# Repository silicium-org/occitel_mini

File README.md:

# [Occitel Mini](https://silicium.org/index.php/edition/occitel-mini-2), production (c)2020..2025 by [Silicium](http://silicium.org)

## TL;DR

[Occitel Mini](https://silicium.org/index.php/edition/occitel-mini-2) is a 1:2 scale reproduction of the original [Occitel](https://silicium.org/index.php/blog-catalogue/pongs/societe-occitane-d-electronique-occitel) game console released in 1976 by the [Société occitane d'électronique](https://fr.wikipedia.org/wiki/Société_occitane_d%27électronique), powered by the then brand-new [General Instruments](https://fr.wikipedia.org/wiki/General_Instrument) [AY-3-8500](https://fr.wikipedia.org/wiki/AY-3-8500) like every Pong-on-a-chip of the same era.

We manufactured a small batch #1, and who knows if there will ever be a batch #2…
Get one from us by [contacting Silicium](https://silicium.org/index.php/contactez-nous) or visit us [IRL at events](https://www.facebook.com/siliciumasso/photos/le-tgs-au-meett-de-toulouse-cétait-du-30-novembre-au-1er-décembre-si-vous-lavez-/1154207946707585/) such as the [Toulouse Game Show](https://tgs-toulouse.fr). \
It comes with a 70-page full color booklet filled with historical data, interviews, new and old photos, in a cardboard package that also is a 1:2 scale reproduction of the original, including cover art that only the connoisseur will know to appreciate…

### QuickStart
- plug into your TV A/V-in with a 75Ω composite lead
- plug in the supplied paddles
- connect a USB Micro-B cable to any power supply
  - caution: Occitel Mini draws _so little_ that a USB power bank may go to sleep
  - you can power and reprogram from any computer running the [Arduino IDE](https://www.arduino.cc/en/software)
- switch on the `game mode` selector
  - you will see 2 LEDs glowing through the case, blinking as the ball hits rackets—if they stop blinking, the software froze ⇒ please file a bug report
  - consult your 1976 Occitel manual regarding other controls
- by default, Occitel Mini emulates the 1976 revision of the AY-3-8500 chip—long-pressing `RàZ` alternates with the 1977 version
- the motherboard has a jumper for NTSC rather than PAL composite video: you may bridge the pads, or solder in a jumper or switch

### Legal
The family of the founder of Société Occitane d'Electronique gave association Silicium permission to reproduce and adapt their designs.

The Occitel book is copyrighted association Silicium in Toulouse, France, licensed under Creative Commons CC-BY-NC-SA.

Grant Searle did not explicit under what license he published his AVRPong a.k.a TVGame 1.5. He wrote "I hope this page has been useful" suggesting it is there for others to use (in other words, he must have meant the opposite of "all rights reserved"), "All information shown here is supplied "as is" with no warranty whatsoever" which is an element of typical licenses but does not grant any rights, "All copyrights recognised" which suggests he recognizes others copyright in prior works he derived his from.

However his Arduino source code is a single file that includes a copy of the Arduino TVout library and its license text, that happens to be the MIT license, therefore we interpret that the whole source code and by extension, the hardware schematics, are released under the MIT license.

The Occitel Mini schematics are a derivative work of Grant Searle's original work, with changes (c)Silicium, combination licensed under the MIT license.

The Occitel source code is a derivative work of TVout by Myles Metzer, with changes (c)Avamander, (c)Grant Searle, (c)members of Silicium (see list in [TL;DR](#tldr)), combination licensed under the MIT license.

The PCB and 3d-printed design are (c)members of Silicium, licensed under CC-BY-NC-SA.

## Changelog
Known bugs: none, unless there is still something wrong with the score in squash (single-player) game ??

Batch #1:
- PCB **1.5.0** (KiCAD 8.0)
- 3d-printed case **2024-11-19** (Fusion 360 -> STEP, STL)
- software **2025-01-11** for SparkFun Pro Micro ATmega32U4 (Arduino IDE 2.3)
- Git tag **1.0** public release and production batch #1

_Authors: Alain Trentin, ben*.* "foobarbaz", François "admin" Pussault, René "El Presidente" Speranza, Sébastien "Sebcbien" Périn, Simon "Nakwada" \
Supermodels: Jeff "Pocket" L., PStriolo_

Initial prototype on [Arduino Leonardo](https://store.arduino.cc/collections/boards-modules/products/arduino-leonardo-with-headers), then [SparkFun Pro Micro](https://www.SparkFun.com/pro-micro-5v-16mhz.html) on breadbord.
Initial schematics on [EasyEDA](https://easyeda.com/).

TODO: easter egg in sleep mode. OC6000 mini with AY-3-8610 emulation using X/Y joysticks on TRRS jacks.

## Design
### Principles of operation
#### The original

The 1976 Occitel is a standard application of the General Instrument AY-3-8500, outputting to a UHF modulator for French TV sets (SECAM 50Hz - there is not much difference with PAL as the Occitel is black&white).
It has an internal speaker and runs off 2 4.5V internal batteries or an external 9V transformer.

 \

Initially it had linear potentiometers in the main case, like the Téléscore 750 from SEB, but apparently it was decided to switch to external paddles, by bolding 3.5mm jack receptacles on the sides, wired in lieu of the integrated linear potentiometers, that were still installed but non-functional - it must have been quicker and less expensive to leave the linear potentiometer in place rather than making new injection molds.

#### The Mini
 \

Grant Searle having reverse-engineered the AY-3-8500 and implemented an emulator for ATmega328, all that was left to do was:
- convert to ATmega32U4 (there are differences in the hardware timers)
- set ball speed and paddle size according to the 3 difficulty settings of the Occitel
- fix a few bugs (the software runs for days, whereas the original crashed after an hour or so - we believe this was due to non-atomic variables shared between background and interrupt contexts).

There is no speaker in the Occitel Mini, instead you get an line-level mono audio output, compatible with any TV set A/V-in.

#### Paddles
 \

Occitel Mini has detachable paddles like the original.
Audio jacks as in the original Occitel are fine for 2-wire RC timing measurement as done by AY-3-8500, but are less than ideal for 3-wire potentiometric measurement as they are prone to shorting the contacts on insertion, which causes arcing between the ground and +5V rails and depending on your USB power supply, may brown out the CPU, causing the video to go out.

That problem is fixed by adding a current-limiting series resistor on the high side of the paddles' potentiometer.

#### Bit-banged composite video
Bit-banged composite video for Arduino was created by Avamander.
ATmega microcontrollers have no DMA and their SPI does not seem to be adequate as a shift register for gap-less pixel rendering, so assembly code toggles a GPIO one pixel at a time, using NOPs for horizontal timing.
Hardware timers are used for vertical timing, so there can be code in the background, and this is where the game logic runs, thus its timing is not critical.
Nonetheless, Pong is simple enough that Grant's code runs at full FPS.

Hardware-wise, we preferred to mix the luminance and sync GPIO outs with diodes (wired-or by diode-resistor logic) rather than pure resistors. This is a change made by JasonKits.

The mixing is passive, relying on the 75Ω termination in the composite video input of the TV set.

If you leave the video output unconnected, voltages will be wrong and an oscilloscope configured for video trigger may fail to recognize the composite sync. Just plug in a screen, or an external termination resistor.

#### ATmega328P vs. ATmega32U4
 \

On ATmega328P, Grant Searle used PB1(OC1A) for SYNC, PB2(OC1B) for VID and PB3(OC2A) for AUD.
Grant's original source code would run on an Arduino Uno wired as SYNC on pin D9, VID on pin D10, AUD on pin D11.

In fact VID and SYNC can be any pins as they are actually not used as OC1x. Also they do not have to be the MSB of a port data register, as imposed by recent versions of the TVout library.

ATmega32U4 does not have 8-bit timer 2 but has timer 0, so we reassigned AUD to timer 0.

Leonardo has a pin for OC0A (PB7 on pin D11) that can serve as AUD, but SparkFun Pro Micro does not.

OC0A is not available on SparkFun Pro Micro, but OC0B is on pin 0. So if OC0A and OC0B are loaded with the same value, timer 0 in CTC mode will do PWM based on OC0A and OC0B will output the toggled waveform same as OC0A (at worst, off by 1 timer increment).

So that is why AUD must be on SparkFun Pro Micro pin 3 (PD0 as OC0B).
VID is PB4 on pin 8 and SYNC is PB5 on pin 9.

On Leonardo, that would be VID on pin D8, SYNC on pin D9. And yes, the SparkFun Pro Micro numbering matches the Leonardo whenever possible.

While not necessary, the Pro Micro technique is compatible with Leonardo, if AUD is on pin D3 (that also is PD0).

### Making your own
- Send the [Gerber](./production_batch_1/occitel_mini-gerber+drill.zip) to JLCPCB or PCBWay etc.
- Solder in the [BoM](./production_batch_1/doc/occitel%20mini%20bom.csv) according to the [schematics](./production_batch_1/doc/occitel%20mini%20sch.pdf) and [layout](./production_batch_1/doc/occitel%20mini%20pcb.pdf)
  - Resistors are 1/8W through-hole or SMD (twin footprints).
  - Diodes are any fast small-signals Si diodes, 1N4007, 1N4148…
  - The audio DC-blocking capacitor can be any value in the μF range.
  - All 3 slide switches are the same SP5T, range-limited by the openings in the case. We found it on AliExpress, see the ["datasheet"](./kicad/1p5t_vertical.jpg). They have to be soldered such that the pins do not protrude from the bottom of the PCB, and the slider caps will be at just the right height. We 3d-printed a jig for holding the SP5T in place while soldering. YMMV…
  - the long-stem (13mm) and right-angle microswitches are common enough. You can use a different length and compensate for the length with the depth of the 3d-printed pushbutton caps.
- Obtain a SparkFun Pro Micro 5V/16MHz or clone and flash the [sketch](./Arduino/occitel_mini/occitel_mini.ino) (see [Contribute](#contribute) if you do not see SparkFun board options in the Arduino IDE).
> [!WARNING]
> The Arduino IDE has no way to know if you have a 8 or 16MHz Pro Micro, which this is critical to USB operation. Unfortunately 8MHz is the 1st menu entry.
> **Be sure to manually set cpu="ATmega32U4 (5V, 16 MHz)"**. Double-check board=="SparkFun Pro Micro" in case the IDE did not detect the USB PID/VID. See below for unbricking.
- Print the [enclosure](./production_batch_1/3d_print/) (the case is a 2-color print, [orange](./production_batch_1/3d_print/boitier.stl) and [white](./production_batch_1/3d_print/serigraphie.stl))
- Solder wires between the female 3.5mm jacks and motherboard (directly or using any connector with 0.1" spacing).
- Slice a 3.5mm audio jack patch cord (male-male) in half and solder each half to a 10kΩ potentiometer, to be installed in each paddle. For easy soldering, use stereo audio cable with individually jacketed left and right wires, not enamel-insulated bare copper strands.
- Assemble with M3x8 self-tapping screws.

### Modifying
- Circuit board: open [`kicad/occitel_mini`](./kicad/occitel_mini/) in [KiCAD](https://www.kicad.org) 8.x
  - beginners may prefer the [EasyEDA](https://easyeda.com/) [standard](https://easyeda.com/editor) or [pro](https://pro.easyeda.com/editor) online editors: import `historical/EasyEDA/SCH_occitel_mini.json` but be warned that the schematics is slightly outdated (no short-circuit protection at the paddle jacks) and was never routed in EasyEDA (routing done only in KiCAD)
  - alternatively, the circuit is easily constructed on a breadbord or perfboard
- Software: copy [`Arduino/occitel_mini/`](./Arduino/occitel_mini/) to your `Arduino/` folder
  - MacOS: `/Users/$USER/Documents/Arduino/`
  - Linux: `/home/$USER/Documents/Arduino/`
  - Windows: `C:\Users\%USERNAME%\Documents\Arduino\`
  - In order to see SparkFun options in the Arduino IDE board manager, you will need to add `https://raw.githubusercontent.com/sparkfun/Arduino_Boards/master/IDE_Board_Manager/package_sparkfun_index.json` to Settings. Or just use `Arduino Leonardo`.

#### Unbricking
If you brick your Pro Micro, [press the reset microswitch twice](https://cdn.SparkFun.com/datasheets/Dev/Arduino/Boards/32U4Note.pdf) within about 0.5s and you will have 8 seconds to press the `Download` button.

If all else fail, the motherboard has the standard Arduino ICSP header (unpopulated—solder a 3x2 HE10 header, or just unplug the Pro Micro module and use DuPont flying leads) that you can use to reflash the bootloader with an [STK500](https://www.microchip.com/en-us/development-tool/atstk500) (just kidding! get an AVR Dragon or the [Olimex AVR-ISP500-TINY](https://www.olimex.com/Products/AVR/Programmers/AVR-ISP500-TINY/)) programmer or the Arduino IDE menu [`Tools > Programmer > Arduino as ISP`](https://docs.arduino.cc/built-in-examples/arduino-isp/ArduinoISP/).

#### Source code
There are 2 compile-time settings:
- `DEBUG_CONSOLE` enables a rudimentary debugger on the serial console, that takes single-character commands `h`, `v`, `o`, `s`, `d`, `r`.
  - while useful if you do no have a DebugWire probe, the Arduino standard library for serial-over-USB appears unreliable in the presence of our direct timer programming, which is non-negociable for bit-banged video generation, so it is what it is.
- `SERIAL_USB_WAIT_DELAY_MS` is 1ms for fastest boot in the production build, but can be set e.g. to 1500ms so that the Arduino IDE serial monitor will have time to capture the early logs.

There are no other compile-time user settings, but you can change many things if you want to add games and depart from strict AY-3-8500 emulation.

You can also run `occitel_mini.ino` on other Arduino boards by selecting adequate assignments of timers and ATmega pins wired to your board's connectors.
See analysis in [ATmega328P vs. ATmega32U4](#atmega328p-vs-atmega32u4) and comments in the source code.

#### Extensibility
ADC pins A2 and A3 are unused (hence why we ran out of inputs for 1976/1977 AY-3-8500 selection) and could be used for 2 more potentiometer, for 4-player Pong, or Occitel OC6000 emulation and its mesmerizing AY-3-8610 soccer game where you can go not just up and down but also left and right… Revolutionary!

Democoders have output color video on ATmega, even on ATtiny.
There are 2 schools, RGB with resistor ladders as a crude DAC, and composite video.
Black&white composite video needs a single GPIO for luminance, and the color RGB resistor ladder technique can be used for greyscale.

PAL/NTSC Color composite is harder because a 4.43MHz color burst is needed for PAL (3.58MHz for NTSC), and then phase lock must be maintained.
This is not realistic on ATmega32U4 that is not fast enough to oversample the color burst by an integer ratio, and whose clock cannot be changed or else USB won't work.

But NTSC has been pulled off by democoders on ATmega328P overclocked to 28MHz by swapping the crystal, yielding a 8x oversampling of the colorburst, enough to obtain a few discrete digital phase shifts, exactly how Woz did it on the Apple II…

At that point, one might as well switch to an ESP32 or STM32 with DMA bit-banged video, or better, a Parallax Propeller or Raspberry Pi Pico (and its XMOS-inspired software-defined signal-shaping coprocessors), or a Raspberry Pi Zero as in the RGB2HDMI…

## Bibliography
### General Instruments AY-3-8500
- [www.pong-story.com](https://www.pong-story.com/gi.htm)
  _trad [fr](https://www-pong--story-com.translate.goog/gi.htm?_x_tr_sl=auto&_x_tr_tl=en&_x_tr_hl=fr&_x_tr_pto=wapp)_
- Occitel Mini would not exist without the amazing [work of Grant Searle](http://searle.x10host.com/AVRPong/index.html)
  _trad [fr](https://searle-x10host-com.translate.goog/AVRPong/index.html?_x_tr_sch=http&_x_tr_sl=auto&_x_tr_tl=en&_x_tr_hl=fr&_x_tr_pto=wapp)_
- Giancarlo Zuliani also did some reverse-engineering: [Analisi del gioco Pong](https://gzuliani.github.io/games/pong-emulator.html)
  _trad [fr](https://gzuliani-github-io.translate.goog/games/pong-emulator.html?_x_tr_sl=auto&_x_tr_tl=fr&_x_tr_hl=fr&_x_tr_pto=wapp)
       [en](https://gzuliani-github-io.translate.goog/games/pong-emulator.html?_x_tr_sl=auto&_x_tr_tl=en&_x_tr_hl=fr&_x_tr_pto=wapp)_
- Joris van Looveren implemented Grant Searle's design on a [custom PCB](http://joris.van-looveren.net/projects/avrpong/)
- JasonKits sells an [assembled board](https://www.tindie.com/products/jasonkits/classic-70s-pong-game/#product-description)
- Reverse engineering by [Cole Johnson](https://nerdstuffbycole.blogspot.com)
  - [Reverse Engineering the AY-3-8500, part 1: Demystifying the Pins](https://nerdstuffbycole.blogspot.com/2018/01/reverse-engineering-ay-3-8500-part-1.html)
  _trad [fr](https://nerdstuffbycole-blogspot-com.translate.goog/2018/01/reverse-engineering-ay-3-8500-part-1.html?_x_tr_sl=auto&_x_tr_tl=en&_x_tr_hl=fr&_x_tr_pto=wapp)_
  - [Building a Simulation of the AY-3-8500](https://nerdstuffbycole.blogspot.com/2018/04/building-simulation-of-ay-3-8500.html)
  _trad [fr](https://nerdstuffbycole-blogspot-com.translate.goog/2018/04/building-simulation-of-ay-3-8500.html?_x_tr_sl=auto&_x_tr_tl=fr&_x_tr_hl=fr&_x_tr_pto=wapp)_
  - [The Simulation is Finally Complete!*](https://nerdstuffbycole.blogspot.com/2018/08/the-simulation-is-finally-complete.html)
  _trad [fr](https://nerdstuffbycole-blogspot-com.translate.goog/2018/08/the-simulation-is-finally-complete.html?_x_tr_sl=auto&_x_tr_tl=fr&_x_tr_hl=fr&_x_tr_pto=wapp)_
  - [Control and Sync Generation in the AY-3-8500](https://nerdstuffbycole.blogspot.com/2018/08/control-and-sync-generation-in-ay-3-8500.html)
  _trad [fr](https://nerdstuffbycole-blogspot-com.translate.goog/2018/08/control-and-sync-generation-in-ay-3-8500.html?_x_tr_sl=auto&_x_tr_tl=fr&_x_tr_hl=fr&_x_tr_pto=wapp)_
  - [Entering the Retrochallenge! (09/2018)](https://nerdstuffbycole.blogspot.com/2018/09/entering-retrochallenge-092018.html)
  _trad [fr](https://nerdstuffbycole-blogspot-com.translate.goog/2018/09/entering-retrochallenge-092018.html?_x_tr_sl=auto&_x_tr_tl=fr&_x_tr_hl=fr&_x_tr_pto=wapp)_
  - [Games and Field Generation in the AY-3-8500](https://nerdstuffbycole.blogspot.com/2018/09/games-and-field-generation-in-ay-3-8500.html)
  _trad [fr](https://nerdstuffbycole-blogspot-com.translate.goog/2018/08/control-and-sync-generation-in-ay-3-8500.html?_x_tr_sl=auto&_x_tr_tl=fr&_x_tr_hl=fr&_x_tr_pto=wapp)_
  - [A visual simulation of the SP0256 (beta)](https://nerdstuffbycole.blogspot.com/2018/09/a-visual-simulation-of-sp0256-beta.html)
  _trad [fr](https://nerdstuffbycole-blogspot-com.translate.goog/2018/09/a-visual-simulation-of-sp0256-beta.html?_x_tr_sl=auto&_x_tr_tl=fr&_x_tr_hl=fr&_x_tr_pto=wapp)_
  - [Shifting bits: How a PONG chip generates on-screen scores](https://nerdstuffbycole.blogspot.com/2018/09/shifting-bits-how-pong-chip-generates.html)
  _trad [fr](https://nerdstuffbycole-blogspot-com.translate.goog/2018/09/shifting-bits-how-pong-chip-generates.html?_x_tr_sl=auto&_x_tr_tl=fr&_x_tr_hl=fr&_x_tr_pto=wapp)_
  - [RetroChallenge 2018 wrap up... and whats next](https://nerdstuffbycole.blogspot.com/2018/10/retrochallenge-2018-wrap-up-and-whats.html)
  _trad [fr](https://nerdstuffbycole-blogspot-com.translate.goog/2018/10/retrochallenge-2018-wrap-up-and-whats.html?_x_tr_sl=auto&_x_tr_tl=fr&_x_tr_hl=fr&_x_tr_pto=wapp)_
  - [Progress update on AY-3-8500 emulation](https://nerdstuffbycole.blogspot.com/2019/01/progress-update-on-ay-3-8500-emulation.html)
  _trad [fr](https://nerdstuffbycole-blogspot-com.translate.goog/2019/01/progress-update-on-ay-3-8500-emulation.html?_x_tr_sl=auto&_x_tr_tl=fr&_x_tr_hl=fr&_x_tr_pto=wapp)_
  - ["Febuary" Progress Update](https://nerdstuffbycole.blogspot.com/2019/03/febuary-progress-update.html)
  _trad [fr](https://nerdstuffbycole-blogspot-com.translate.goog/2019/03/febuary-progress-update.html?_x_tr_sl=auto&_x_tr_tl=fr&_x_tr_hl=fr&_x_tr_pto=wapp)_
  - [The AY-3-8606, another successfully simulated circuit](https://nerdstuffbycole.blogspot.com/2019/03/the-ay-3-8606-another-successfully.html)
  _trad [fr](https://nerdstuffbycole-blogspot-com.translate.goog/2019/03/the-ay-3-8606-another-successfully.html?_x_tr_sl=auto&_x_tr_tl=fr&_x_tr_hl=fr&_x_tr_pto=wapp)_
  - [Playable emulation, and more!](https://nerdstuffbycole.blogspot.com/2019/07/playable-emulation-and-more.html)
  _trad [fr](https://nerdstuffbycole-blogspot-com.translate.goog/2019/07/playable-emulation-and-more.html?_x_tr_sl=auto&_x_tr_tl=fr&_x_tr_hl=fr&_x_tr_pto=wapp)_
  - [Shooter game in silicon: inside the AY-3-8605 chip](https://nerdstuffbycole.blogspot.com/2019/10/shooter-game-in-silicon-inside-ay-3.html)
  _trad [fr](https://nerdstuffbycole-blogspot-com.translate.goog/2019/10/shooter-game-in-silicon-inside-ay-3.html?_x_tr_sl=auto&_x_tr_tl=fr&_x_tr_hl=fr&_x_tr_pto=wapp)_
  - [End of year update](https://nerdstuffbycole.blogspot.com/2020/01/end-of-year-update.html)
  _trad [fr](https://nerdstuffbycole-blogspot-com.translate.goog/2020/01/end-of-year-update.html?_x_tr_sl=auto&_x_tr_tl=fr&_x_tr_hl=fr&_x_tr_pto=wapp)_

### Bit-banged video composite generation on Arduino
- Avamander's finely crafted [Arduino-TVout](https://github.com/Avamander/arduino-tvout)
- If you want to do color RGB, have a look at the [Craft demo by Ift](https://www.linusakesson.net/scene/craft/) (release at [pouet.net](https://www.pouet.net/prod.php?which=50141))

### Datasheets
- General Instrument's AY-3-8500 "pong-on-a-chip"
  - [short datasheet](https://www.raphnet.net/divers/tvfun_repair/AY-3-8500.pdf) and [full datasheet](https://www.qsl.net/yt2fsg/games/AY-3-8500_12.pdf), also at [Internet Archive](https://archive.org/details/ay-3-8500-12/mode/2up)
  - [1978 catalog](https://www.pong-story.com/GIMINI1978.pdf)
- SparkFun [Pro Micro 5V/16MHz](https://www.SparkFun.com/pro-micro-5v-16mhz.html#documentation)
  - [how to unbrick](https://cdn.SparkFun.com/datasheets/Dev/Arduino/Boards/32U4Note.pdf)
  - [pinout](https://cdn.SparkFun.com/assets/f/d/8/0/d/ProMicro16MHzv2.pdf)
- [Pinout](https://docs.arduino.cc/resources/pinouts/A000057-full-pinout.pdf) of Arduino [Leonardo](https://docs.arduino.cc/hardware/leonardo/
), [pinout](https://content.arduino.cc/assets/Pinout-UNOrev3_latest.pdf) of Arduino [Uno](https://docs.arduino.cc/retired/boards/arduino-uno-rev3-with-long-pins/)
- Arduino Leonardo and SparkFun Pro Micro use the [ATmega32U4](https://www.microchip.com/en-us/product/atmega32u4)
  - [datasheet](https://ww1.microchip.com/downloads/en/DeviceDoc/Atmel-7766-8-bit-AVR-ATmega16U4-32U4_Datasheet.pdf) and [summary](https://ww1.microchip.com/downloads/en/DeviceDoc/Atmel-7766-8-bit-AVR-ATmega16U4-32U4_Summary.pdf)
  - [AVR8 Instruction Set Manual](https://ww1.microchip.com/downloads/aemDocuments/documents/MCU08/ProductDocuments/ReferenceManuals/AVR-InstructionSet-Manual-DS40002198.pdf)
  - Application Notes of interest:
    - [AN035 Efficient C Coding for AVR](https://ww1.microchip.com/downloads/aemDocuments/documents/OTH/ApplicationNotes/ApplicationNotes/doc1497.pdf)
    - [AN4027 Tips and Tricks to Optimize Your C Code for 8-bit AVR Microcontrollers](https://ww1.microchip.com/downloads/aemDocuments/documents/OTH/ApplicationNotes/ApplicationNotes/doc8453.pdf)
    - [AN1886 Mixing Assembly and C with AVRGCC](https://ww1.microchip.com/downloads/aemDocuments/documents/OTH/ApplicationNotes/ApplicationNotes/doc42055.pdf)
    - [AN072 Accessing 16-bit I/O Registers](https://ww1.microchip.com/downloads/aemDocuments/documents/OTH/ApplicationNotes/ApplicationNotes/doc1493.pdf)
    - [AN130 Setup and Use of AVR Timers](https://ww1.microchip.com/downloads/aemDocuments/documents/OTH/ApplicationNotes/ApplicationNotes/Atmel-2505-Setup-and-Use-of-AVR-Timers_ApplicationNote_AVR130.pdf)

../..
<!-- markdownlint-disable-file blank_lines -->
<!-- vim: set shiftwidth=2 softtabstop=2 expandtab : -->

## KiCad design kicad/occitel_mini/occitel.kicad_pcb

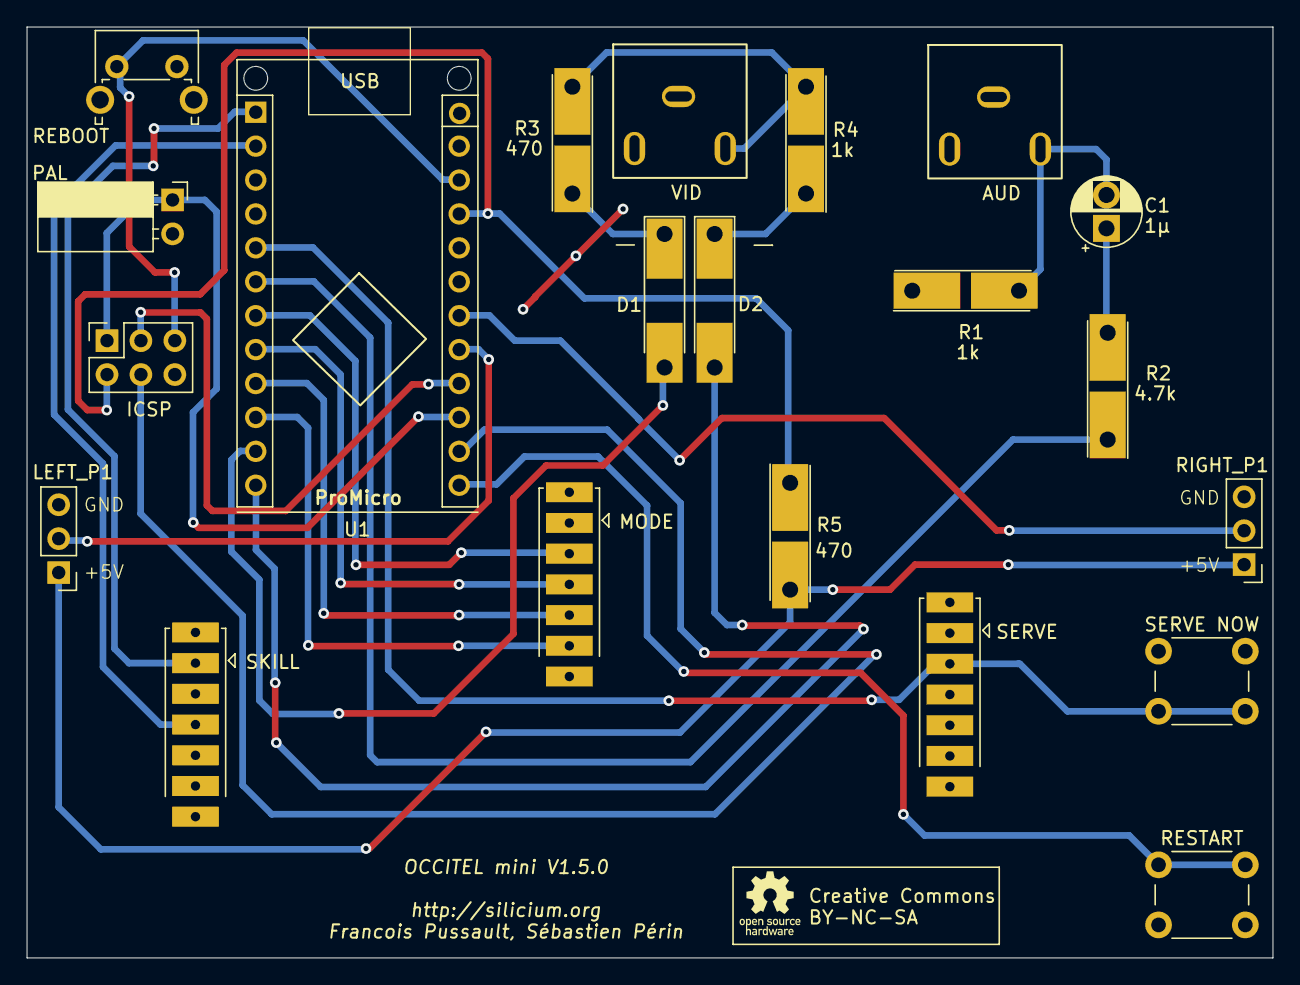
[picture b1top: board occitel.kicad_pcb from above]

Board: 2 copper layers, 93.3 x 69.7 mm, 21 parts (0 on the bottom side), 25 nets.

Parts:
AUD: RCA_AUDIO; RCA_3_2+1
C1: 1µ; CP_Radial_D5.0mm_P2.50mm
D1, D2: 1n4007; D_MELF-RM10_Universal_Handsoldering
ICSP: ICSP; PinSocket_2x03_P2.54mm_Vertical
LEFT_P1: pin_L_player; PinHeader_1x03_P2.54mm_Vertical
MODE: GameMode; BG_SPDT_5
PAL: Conn_01x02_Socket; PinSocket_1x02_P2.54mm_Horizontal
R1, R4: 1k; RLC_with_both_THTSMD
R2: 4.7k; RLC_with_both_THTSMD
R3, R5: 470; RLC_with_both_THTSMD
REBOOT: System REBOOT; SW_Tactile_SPST_Angled_PTS645Vx83-2LFS
RESTART: System Restart; SW_PUSH_6mm_H13mm
RIGHT_P1: pin_R_player; PinHeader_1x03_P2.54mm_Vertical
SERVE: serve_auto_now; BG_SPDT_5
SERVE NOW: ServeNow; SW_PUSH_6mm_H13mm
SKILL: Difficulty; BG_SPDT_5
U1: ProMicro; Arduino_PROMICRO
VID: RCA_VIDEO; RCA_3_2+1

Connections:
+5V: ICSP.2, R5.1, U1.21 (VCC)
GND: AUD.2 (Ext), ICSP.6, LEFT_P1.3, MODE.1 (select), PAL.2, R1.1, REBOOT.2, RESTART.2, RIGHT_P1.3, SERVE.1 (select), SERVE NOW.1, SKILL.1 (select), U1.3 (GND), U1.4 (GND), U1.23 (GND), VID.2 (Ext)
ICSP_3: ICSP.3, U1.16 (B1)
ICSP_4: ICSP.4, U1.14 (B2)
L_player: LEFT_P1.2, U1.17 (F7)
unnamed: C1.1, R2.2
unnamed: D1.1 (K), R3.1
unnamed: D2.1 (K), R4.1
unnamed: AUD.1 (In), C1.2, R1.2
unnamed: R3.2, R4.2, VID.1 (In)
unnamed: LEFT_P1.1, R5.2, RIGHT_P1.1
PAL: ICSP.1, PAL.1, U1.15 (B3)
R_player: RIGHT_P1.2, U1.18 (F6)
Squash: MODE.5 (4), U1.9 (D7)
VID: D1.2 (A), U1.11 (B4)
Vsync: D2.2 (A), U1.12 (B5)
amat: SKILL.4, U1.2 (RX)
audio: R2.1, U1.6 (SCL)
football: MODE.4, U1.8 (C6)
noob: SKILL.2 (1), U1.1 (TX)
reset: ICSP.5, REBOOT.1, U1.22 (RST)
restart: RESTART.1, U1.13 (B6)
serve: SERVE.3 (1), SERVE NOW.2, U1.5 (SDA)
tennis: MODE.3 (1), U1.7 (D4)
training: MODE.6 (5), U1.10 (E6)

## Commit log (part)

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2025-01-24 public release for production batch #1
